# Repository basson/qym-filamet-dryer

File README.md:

# qym-filamnet-dryer

DIY filament dryer

Сушилка на 3 катушки, с возможностью печатать сразу из сушилки.

Помещаться должны самые большие катушки размеры которых я нашел.

Максимальная ширина катушки 98мм максимальный диаметр катушки 215мм.

Проект находится в стадии разработки.

Вся разработка ведётся на стримах.

Следить за проектом можно на моем канале YouTube:

https://www.youtube.com/playlist?list=PLECrWHz_TG886tEzgreLgq92PoEziWuON

# Планируемый функционал:

* Контроль температуры и влажности.
* Таймеры для сушки.
* Разные алгоритмы сушики пластика.
* Интеграция в klipper для управления из него.
* Для владельцев Flying Bear GHost 6 есть возможность установки сушилки вторым этажом прям на колпак принтера. (Колпак пилится одновременно с сушилкой и скоро тоже появится у меняв репозиториях)

---

**Что имеем сейчас:**

В папках stl, cad, draft чертежи для раскроя панелей на CO2 лазере, модели для печатных деталей и step фалы если кто-то решит что, то поправить.

Что будем делать на стримах:

* Проектировать плату в Kicad (схема уже накидана).
* Писать прошивку для управления сушилкой.
* Делать интеграцию в Klipper.
* Печать всех деталей для новой версии сборка и тесты сушилки.

---

**Подписывайся на мой youtube канал я там стараюсь вести регулярные стримы по всем своим проектам!!**

YouTube Transalations - https://www.youtube.com/@basson_xvi/streams

Thingiverse - https://www.thingiverse.com/thing:6427349

Printables - https://www.printables.com/model/716319-flying-bear-ghost-6-slim-skirt-for-electronics-pla

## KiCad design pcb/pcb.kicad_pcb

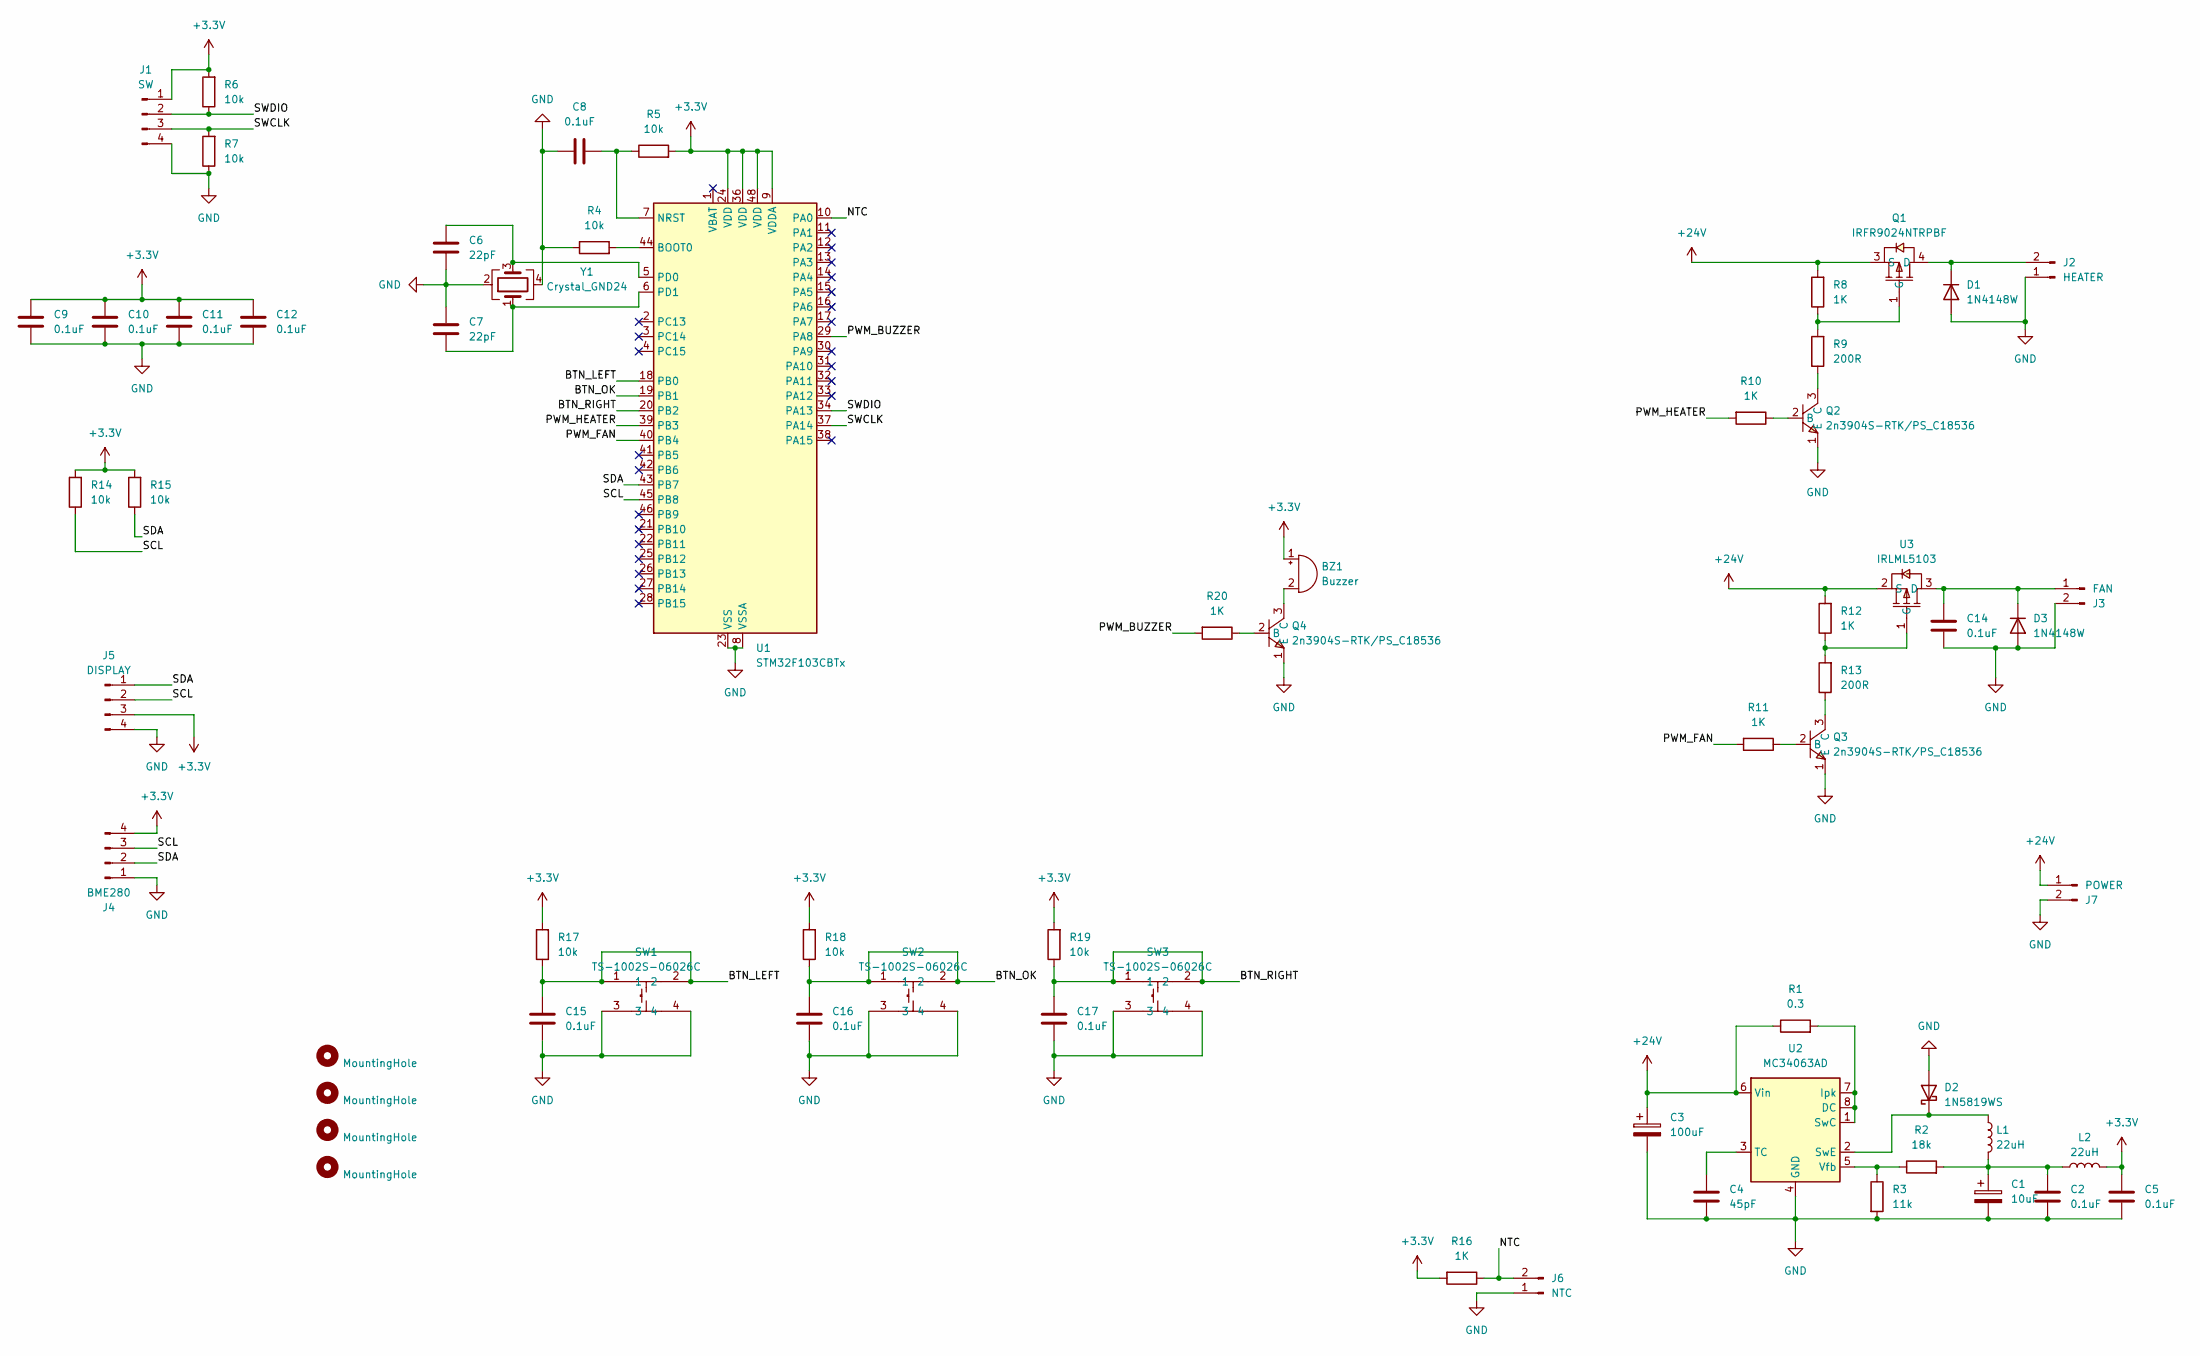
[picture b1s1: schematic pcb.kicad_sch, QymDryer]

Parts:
BZ1: Buzzer; Buzzer_12x9.5RM7.6
C1: 10uF; CP_Radial_D5.0mm_P2.50mm
C2, C5, C8, C9, C10, C11, C12, C14, C15, C16, C17: 0.1uF; C_1206_3216Metric_Pad1.33x1.80mm_HandSolder
C3: 100uF; CP_Radial_D8.0mm_P5.00mm
C4: 45pF; C_1206_3216Metric_Pad1.33x1.80mm_HandSolder
C6, C7: 22pF; C_1206_3216Metric_Pad1.33x1.80mm_HandSolder
D1, D3: 1N4148W; D_SOD-123
D2: 1N5819WS; D_2114_3652Metric_Pad1.85x3.75mm_HandSolder
H1, H2, H3, H4: MountingHole; MountingHole_3.2mm_M3_DIN965_Pad
J1: SW; PinHeader_1x04_P2.54mm_Vertical
J2: HEATER; TerminalBlock_Phoenix_MKDS-1,5-2_1x02_P5.00mm_Horizontal
J3: FAN; CONN-TH_2P-P2.50_HC-XH-2A-G
J4: BME280; CONN-TH_4P-P2.50_HC-XH-4A-G
J5: DISPLAY; Display_128x64_096_I2C
J6: NTC; CONN-TH_2P-P2.50_HC-XH-2A-G
J7: POWER; TerminalBlock_Phoenix_MKDS-1,5-2_1x02_P5.00mm_Horizontal
L1: 22uH; L_6.3x6.3_H3
L2: 22uH; L_1206_3216Metric_Pad1.22x1.90mm_HandSolder
Q1: IRFR9024NTRPBF; TO-252-2_L6.6-W6.1-P4.58-LS9.9-TR; LCSC Part C2585
Q2, Q3, Q4: 2n3904S-RTK/PS_C18536; SOT-23-3_L2.9-W1.3-P1.90-LS2.4-TR; LCSC Part C18536
R1: 0.3; R_1206_3216Metric_Pad1.30x1.75mm_HandSolder
R2: 18k; R_1206_3216Metric_Pad1.30x1.75mm_HandSolder
R3: 11k; R_1206_3216Metric_Pad1.30x1.75mm_HandSolder
R4, R5, R6, R7, R14, R15, R17, R18, R19: 10k; R_1206_3216Metric_Pad1.30x1.75mm_HandSolder
R8, R10, R11, R12, R16, R20: 1K; R_1206_3216Metric_Pad1.30x1.75mm_HandSolder
R9, R13: 200R; R_1206_3216Metric_Pad1.30x1.75mm_HandSolder
SW1, SW2, SW3: TS-1002S-06026C; KEY-SMD_4P-L6.0-W6.0-P4.50-LS9.5-BR; LCSC Part C455112
U1: STM32F103CBTx; LQFP-48_7x7mm_P0.5mm
U2: MC34063AD; SOIC-8_3.9x4.9mm_P1.27mm
U3: IRLML5103; SOT-23-3_L3.0-W1.7-P0.95-LS2.9-BR; LCSC Part C5364309
Y1: Crystal_GND24; Crystal_SMD_5032-4Pin_5.0x3.2mm

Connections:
+3.3V: BZ1.1 (-), C5.1, C9.2, C10.2, C11.2, C12.2, J1.1, J4.4, J5.3, L2.2, R5.2, R6.2, R14.2, R15.2, R16.2, R17.2, R18.2, R19.2, U1.9 (VDDA), U1.24 (VDD), U1.36 (VDD), U1.48 (VDD)
+24V: C3.1, J7.1, Q1.3 (S), R1.1, R8.2, R12.2, U2.6 (Vin), U3.2 (S)
/BTN_LEFT: C15.2, R17.1, SW1.1, SW1.2, U1.18 (PB0)
/BTN_OK: C16.2, R18.1, SW2.1, SW2.2, U1.19 (PB1)
/BTN_RIGHT: C17.2, R19.1, SW3.1, SW3.2, U1.20 (PB2)
/NTC: J6.2, R16.1, U1.10 (PA0)
/PWM_BUZZER: R20.2, U1.29 (PA8)
/PWM_FAN: R11.2, U1.40 (PB4)
/PWM_HEATER: R10.2, U1.39 (PB3)
/SCL: J4.3, J5.2, R14.1, U1.45 (PB8)
/SDA: J4.2, J5.1, R15.1, U1.43 (PB7)
/SWCLK: J1.3, R7.2, U1.37 (PA14)
/SWDIO: J1.2, R6.1, U1.34 (PA13)
GND: C1.2, C2.2, C3.2, C4.2, C5.2, C6.1, C7.1, C8.1, C9.1, C10.1, C11.1, C12.1, C14.2, C15.1, C16.1, C17.1, D1.2 (A), D2.2 (A), D3.2 (A), J1.4, J2.1, J3.2, J4.1, J5.4, J6.1, J7.2, Q2.1 (E), Q3.1 (E), Q4.1 (E), R3.2, R4.1, R7.1, SW1.3, SW1.4, SW2.3, SW2.4, SW3.3, SW3.4, U1.8 (VSSA), U1.23 (VSS), U1.35 (VSS), U1.47 (VSS), U2.4 (GND), Y1.2, Y1.4
unnamed: BZ1.2 (+), Q4.3 (C)
unnamed: C1.1, C2.1, L1.2, L2.1, R2.2
unnamed: D1.1 (K), J2.2, Q1.4 (D)
unnamed: D2.1 (K), L1.1, U2.2 (SwE)
unnamed: C14.1, D3.1 (K), J3.1, U3.3 (D)
unnamed: Q1.1 (G), R8.1, R9.2
unnamed: Q2.2 (B), R10.1
unnamed: Q2.3 (C), R9.1
unnamed: Q3.2 (B), R11.1
unnamed: Q3.3 (C), R13.1
unnamed: Q4.2 (B), R20.1
unnamed: R4.2, U1.44 (BOOT0)
unnamed: C8.2, R5.1, U1.7 (NRST)
unnamed: C6.2, U1.5 (PD0), Y1.3
unnamed: C7.2, U1.6 (PD1), Y1.1
unnamed: R1.2, U2.1 (SwC), U2.7 (Ipk), U2.8 (DC)
unnamed: C4.1, U2.3 (TC)
unnamed: R2.1, R3.1, U2.5 (Vfb)
unnamed: R12.1, R13.2, U3.1 (G)

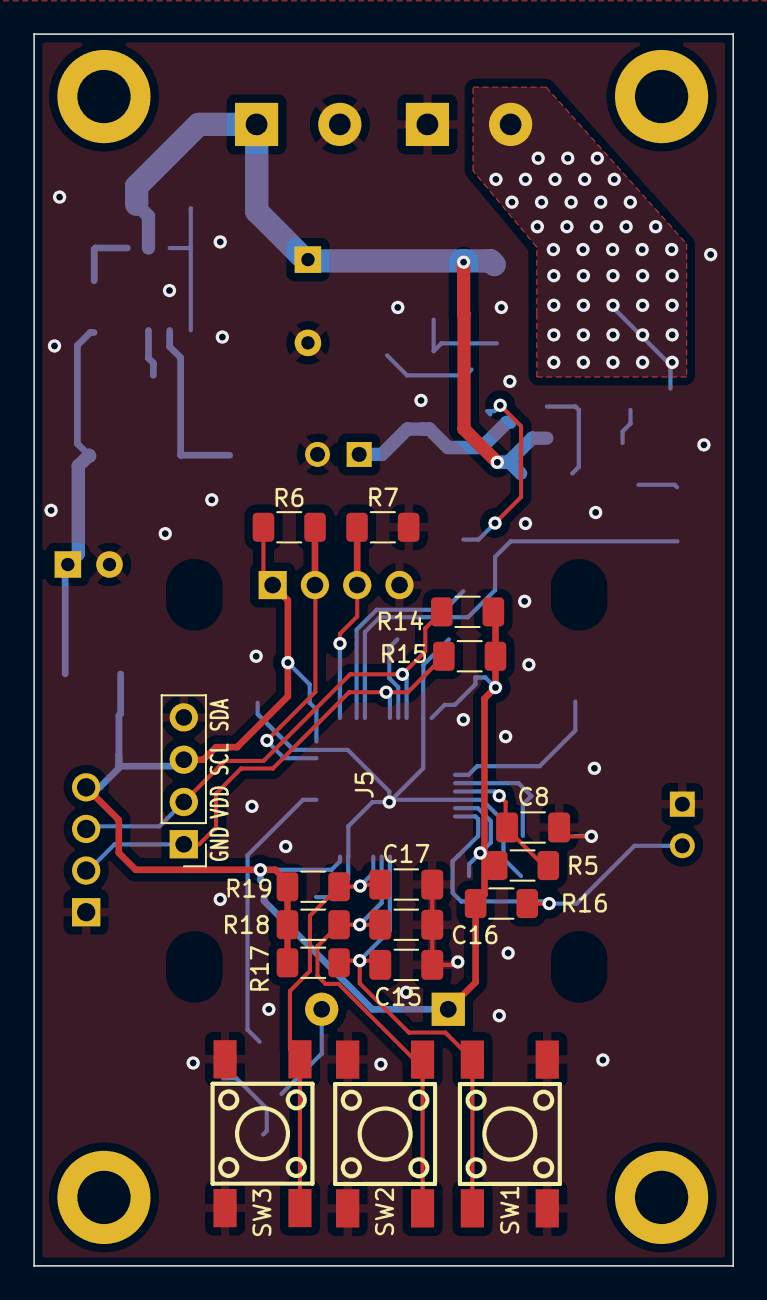
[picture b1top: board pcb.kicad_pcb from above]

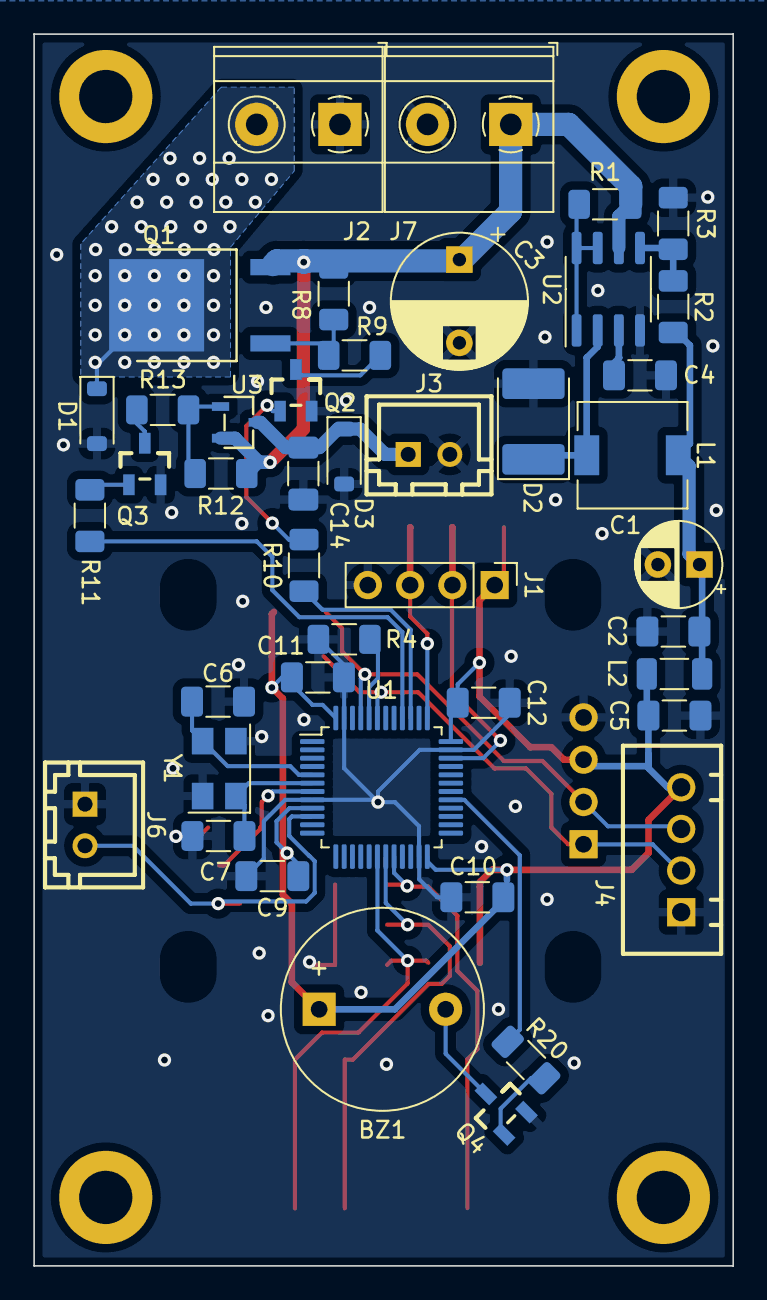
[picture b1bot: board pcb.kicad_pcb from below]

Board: 2 copper layers, 42.0 x 74.0 mm, 64 parts (43 on the bottom side), 33 nets.

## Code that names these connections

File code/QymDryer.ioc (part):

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Mcu.Name=STM32F103C(8-B)Tx
Mcu.Package=LQFP48
Mcu.UserName=STM32F103CBTx
PA0-WKUP.GPIOParameters=GPIO_Label
PA0-WKUP.GPIO_Label=NTC
PA0-WKUP.Signal=ADCx_IN0
PA13.Mode=Serial_Wire
PA13.Signal=SYS_JTMS-SWDIO
PA14.Mode=Serial_Wire
PA14.Signal=SYS_JTCK-SWCLK
PA8.GPIOParameters=GPIO_Label
PA8.GPIO_Label=PWM_BUZZER
PA8.Signal=S_TIM1_CH1
PB0.GPIOParameters=GPIO_Label,GPIO_ModeDefaultEXTI
PB0.GPIO_Label=BTN_LFET
PB0.GPIO_ModeDefaultEXTI=GPIO_MODE_EVT_FALLING
PB0.Signal=GPXTI0
PB1.GPIOParameters=GPIO_Label,GPIO_ModeDefaultEXTI
PB1.GPIO_Label=BTN_OK
PB1.GPIO_ModeDefaultEXTI=GPIO_MODE_EVT_FALLING
PB1.Signal=GPXTI1
PB2.GPIOParameters=GPIO_Label,GPIO_ModeDefaultEXTI
PB2.GPIO_Label=BTN_RIGHT
PB2.GPIO_ModeDefaultEXTI=GPIO_MODE_EVT_FALLING
PB2.Signal=GPXTI2
PB3.GPIOParameters=GPIO_Label
PB3.GPIO_Label=PWM_HEATER
PB3.Signal=S_TIM2_CH2
PB4.GPIOParameters=GPIO_Speed,GPIO_Label
PB4.GPIO_Label=PWM_FAN
PB4.GPIO_Speed=GPIO_SPEED_FREQ_HIGH
PB4.Signal=S_TIM3_CH1
PB6.GPIOParameters=GPIO_Label
PB6.GPIO_Label=SCL
PB6.Mode=I2C
PB6.Signal=I2C1_SCL
PB7.GPIOParameters=GPIO_Label
PB7.GPIO_Label=SDA
PB7.Mode=I2C
PB7.Signal=I2C1_SDA
PD0-OSC_IN.Mode=HSE-External-Oscillator
PD0-OSC_IN.Signal=RCC_OSC_IN
PD1-OSC_OUT.Mode=HSE-External-Oscillator
PD1-OSC_OUT.Signal=RCC_OSC_OUT
RCC.SYSCLKFreq_VALUE=72000000
RCC.SYSCLKSource=RCC_SYSCLKSOURCE_PLLCLK
board=custom

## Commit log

2024-01-19 Все наработки по сушлке на данный момент.
2024-01-21 Work with schematics and pcb. update *.ioc files at project.
2024-01-27 Work in pcb placment components
2024-01-28 Update display ss1306 footprint. paste text refrenece on pcb
2024-01-31 Add fitting nut and initalize code from control board firmware
